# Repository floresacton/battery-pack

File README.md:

# battery-pack
Li-Ion 21700 12S3P Pack

## notes
Battery will have onboard 12V buck regulator for aux power (5A-10A)
This will also have double gated 12V to external aux power

12V -> 5V buck regulator for mini aux power (VCC self power effeciency and for BMS util)

BMS takes in 5V and LDO to 3V3

Main BMS: read all cell voltages, balancing, current measure, and dual gate disconnect, temperature
put one thermistor on the board and some on the cells

On the back of the BMS and maybe the regulator, the thermistor connections to measure cell temps

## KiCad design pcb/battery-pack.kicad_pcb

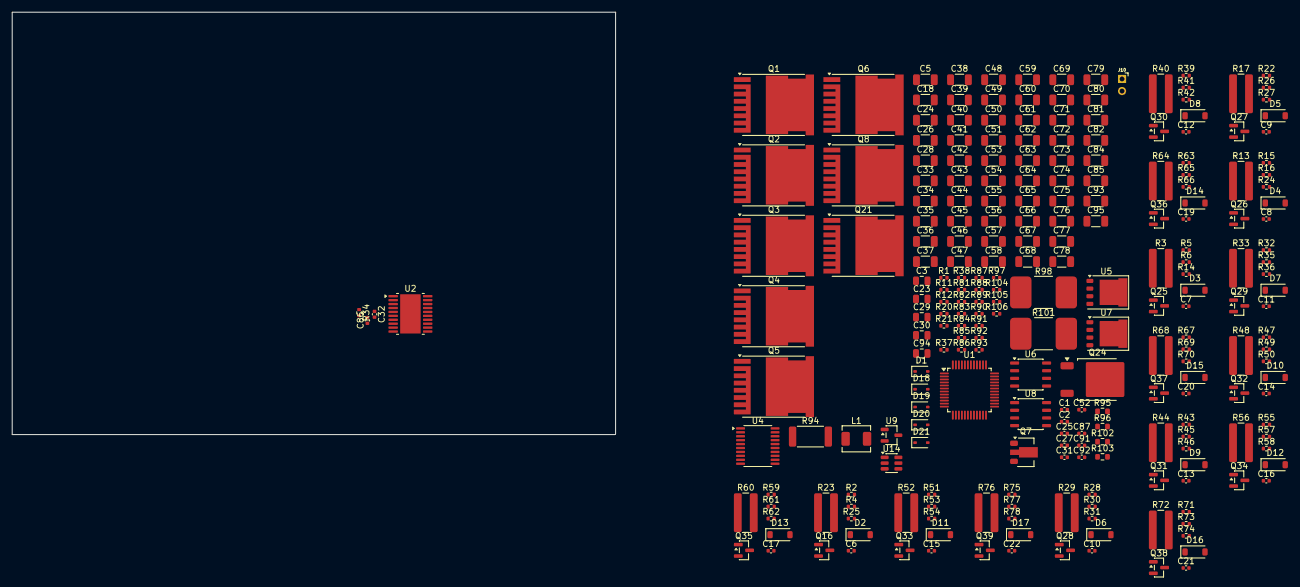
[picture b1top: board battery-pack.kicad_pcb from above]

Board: 4 copper layers, 100.0 x 70.0 mm, 244 parts (0 on the bottom side), 120 nets, no tracks yet.

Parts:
C1, C6, C7, C8, C9, C10, C11, C12, C13, C14, C15, C16, C17, C19, C20, C21, C22, C25, C27, C52, C91, C92: 100n; C_0402_1005Metric
C2, C31: 100p; C_0402_1005Metric
C3, C23, C29, C30, C94: 1u; C_0805_2012Metric
C5, C24, C39, C40, C45, C46, C51, C53, C58, C59, C63, C64, C65, C66, C67, C68, C69, C70, C71, C72, C73, C74, C75, C76, C77, C78, C79, C80, C81, C82, C84, C85: 2u2; C_1206_3216Metric
C18, C26, C28, C33, C34, C35, C36, C37, C38, C41, C42, C43, C44, C47, C48, C49, C50, C54, C55, C56, C57, C60, C61, C62, C93, C95: 10u; C_1206_3216Metric
C32: 1n; C_0402_1005Metric
C86: 10n; C_0402_1005Metric
C87: 2n2; C_0402_1005Metric
D1, D18, D19, D20, D21: 1N4148WS; D_SOD-323
D2, D3, D4, D5, D6, D7, D8, D9, D10, D11, D12, D13, D14, D15, D16, D17: BZT52C5V6; D_SOD-123
J10: Conn_01x02; 1x02_2.00mm_Solder
L1: 4u7; L_TechFuse_SL0420
Q1, Q2, Q3, Q4, Q5, Q6, Q8, Q21: SP010N01BGHTO; Infineon_PG-HSOF-8-1
Q7: CXT5551; SOT-89-3
Q16, Q25, Q26, Q27, Q28, Q29, Q30, Q31, Q32, Q33, Q34, Q35, Q36, Q37, Q38, Q39: HL2300; SOT-23
Q24: AGM150P10D; TO-252-2
R1, R2, R5, R6, R11, R12, R15, R16, R22, R25, R27, R28, R31, R32, R36, R39, R42, R43, R46, R47, R50, R51, R54, R55, R58, R59, R62, R63, R66, R67, R70, R71, R74, R75, R78, R85, R86, R87, R88, R89: 100; R_0402_1005Metric
R3, R13, R17, R23, R29, R33, R40, R44, R48, R52, R56, R60, R64, R68, R72, R76: 8; R_1225_3264Metric
R4, R14, R20, R21, R24, R26, R30, R35, R38, R41, R45, R49, R53, R57, R61, R65, R69, R73, R77, R81, R82, R83, R84, R90, R92: 2k; R_0402_1005Metric
R34, R104: 12k; R_0402_1005Metric
R37: 22k; R_0402_1005Metric
R91, R93, R97, R105: 33k; R_0402_1005Metric
R94: 3m; R_2512_6332Metric
R95, R96, R102, R103: 1; R_0603_1608Metric
R98, R101: 1m; R_Shunt_3921
R106: 2k2; R_0402_1005Metric
U1: BQ7695202; TQFP-48_7x7mm_P0.5mm
U2: LM5116; HTSSOP-20-1EP_4.4x6.5mm_P0.65mm_EP3.4x6.5mm_Mask2.4x3.7mm
U4: STM32C011F6Px; TSSOP-20_4.4x6.5mm_P0.65mm
U5, U7: AGM042N10A; PQFN-8-EP_6x5mm_P1.27mm_Generic
U6: SP485E; JEITA_SOIC-8_3.9x4.9mm_P1.27mm
U8: IRS2181STR; JEITA_SOIC-8_3.9x4.9mm_P1.27mm
U9: XC6206PxxxMR; SOT-23-3
U14: JW5017S; SOT-23-6

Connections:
+3V3: C23.1, D18.1 (K), R20.2, R21.2, U1.35 (REG1), U4.4 (VDD)
+5V: C26.1, C52.2, C92.2, C93.1, C95.1, L1.2, R104.2, U6.8 (VCC), U9.3 (VI)
+15V: C28.1, C34.1, C35.1, C36.1, C37.1, C38.1, C41.1, C42.1, C43.1, C44.1, C47.1, C48.1, C49.1, C50.1, C54.1, C55.1, C56.1, C57.1, C60.1, C61.1, C62.1, D19.2 (A), R37.2, R105.2, U2.10 (VOUT), U2.17 (VCCX), U8.5 (VCC), U14.5 (VIN)
/BREG: Q7.1 (B), U1.37 (BREG)
/BST: C33.1, D19.1 (K), U8.8 (VB)
/BT: C91.1, U14.1 (BST)
/CL1: D3.2 (A), Q25.2 (S), R2.2, R5.2, R23.1
/CL2: D4.2 (A), Q26.2 (S), R3.1, R6.2, R15.2
/CL3: D5.2 (A), Q27.2 (S), R13.1, R16.2, R27.2
/CL4: D6.2 (A), Q28.2 (S), R17.1, R22.2, R31.2
/CL5: D7.2 (A), Q29.2 (S), R28.2, R29.1, R36.2
/CL6: D8.2 (A), Q30.2 (S), R32.2, R33.1, R42.2
/CL7: D9.2 (A), Q31.2 (S), R39.2, R40.1, R46.2
/CL8: D10.2 (A), Q32.2 (S), R43.2, R44.1, R50.2
/CL9: D11.2 (A), Q33.2 (S), R47.2, R48.1, R54.2
/CL10: D12.2 (A), Q34.2 (S), R51.2, R52.1, R58.2
/CL11: D13.2 (A), Q35.2 (S), R55.2, R56.1, R62.2
/CL12: D14.2 (A), Q36.2 (S), R59.2, R60.1, R66.2
/CL13: D15.2 (A), Q37.2 (S), R63.2, R64.1, R70.2
/CL14: D16.2 (A), Q38.2 (S), R67.2, R68.1, R74.2
/CL15: D17.2 (A), Q39.2 (S), R71.2, R72.1, R78.2
/CMP: C31.1, R97.2, U2.9 (COMP)
/CP: C3.1, U1.46 (CP1)
/CS: R94.1, U2.12 (CS), U5.1 (S), U5.2 (S), U5.3 (S)
/DSG: Q1.1 (G), Q8.1 (G), Q21.1 (G), U1.43 (DSG)
/FB: C31.2, C87.1, R37.1, R38.2, R104.1, R106.1, U2.8 (FB), U14.3 (FB)
/GCH: R103.1, U8.7 (HO)
/GCL: R102.1, U8.4 (LO)
/GD: Q3.1 (G), Q4.1 (G)
/GH: Q2.1 (G), Q5.1 (G), R103.2
/HB: C30.1, D20.1 (K), U2.18 (HB)
/HO: R96.1, U2.19 (HO)
/LD: R82.1, U1.41 (LD)
/LO: R95.1, U2.15 (LO)
/PACK: R81.1, U1.42 (PACK)
/PH: C33.2, Q2.2 (S), Q5.2 (S), Q6.3 (D), U8.6 (VS)
/RAMP: C32.1, U2.5 (RAMP)
/REG18: C18.1, U1.24 (REG18)
/REGIN: C25.2, Q7.3 (E), U1.36 (REGIN)
/RSA: J10.2, R88.2, R89.2, U6.6 (A)
/RSB: J10.1, R86.1, R87.1, U6.7 (B)
/RT: R34.1, U2.3 (RT)
/SCL: R20.1, U1.26 (SCL)
/SDA: R21.1, U1.27 (SDA)
/SPL: C27.2, R86.2, R87.2, R88.1, R89.1
/SRN: C1.1, C2.1, R12.1, U1.20 (SRN)
/SRP: C1.2, C2.2, R11.1, U1.18 (SRP)
/SS: C86.1, U2.7 (SS)
/SW: C30.2, C91.2, L1.1, U2.20 (SW), U5.5 (D), U7.1 (S), U7.2 (S), U7.3 (S), U14.6 (SW)
/UVLO: R91.1, R92.2, U2.2 (UVLO)
/VC0: C6.1, R4.1, R25.1, U1.16 (VC0)
/VC1: C6.2, C7.1, R2.1, R5.1, R14.1, U1.15 (VC1)
/VC2: C7.2, C8.1, R6.1, R15.1, R24.1, U1.14 (VC2)
/VC3: C8.2, C9.1, R16.1, R26.1, R27.1, U1.13 (VC3)
/VC4: C9.2, C10.1, R22.1, R30.1, R31.1, U1.12 (VC4)
/VC5: C10.2, C11.1, R28.1, R35.1, R36.1, U1.11 (VC5)
/VC6: C11.2, C12.1, R32.1, R41.1, R42.1, U1.10 (VC6)
/VC7: C12.2, C13.1, R39.1, R45.1, R46.1, U1.9 (VC7)
/VC8: C13.2, C14.1, R43.1, R49.1, R50.1, U1.8 (VC8)
/VC9: C14.2, C15.1, R47.1, R53.1, R54.1, U1.7 (VC9)
/VC10: C15.2, C16.1, R51.1, R57.1, R58.1, U1.6 (VC10)
/VC11: C16.2, C17.1, R55.1, R61.1, R62.1, U1.5 (VC11)
/VC12: C17.2, C19.1, R59.1, R65.1, R66.1, U1.4 (VC12)
/VC13: C19.2, C20.1, R63.1, R69.1, R70.1, U1.3 (VC13)
/VC14: C20.2, C21.1, R67.1, R73.1, R74.1, U1.2 (VC14)
/VC15: C21.2, C22.1, R71.1, R77.1, R78.1, U1.1 (VC15)
/VC16: C22.2, R75.1, U1.48 (VC16)
/VCCR: C29.1, D20.2 (A), U2.16 (VCC)
GBAT: C5.2, C18.2, C23.2, C24.2, C25.1, D2.2 (A), Q16.2 (S), R11.2, R25.2, R90.1, U1.17 (VSS), U1.34 (REG2), U1.38 (FUSE)
GND: C26.2, C27.1, C28.2, C29.2, C32.2, C34.2, C35.2, C36.2, C37.2, C38.2, C39.2, C40.2, C41.2, C42.2, C43.2, C44.2, C45.2, C46.2, C47.2, C48.2, C49.2, C50.2, C51.2, C52.1, C53.2, C54.2, C55.2, C56.2, C57.2, C58.2, C59.2, C60.2, C61.2, C62.2, C63.2, C64.2, C65.2, C66.2, C67.2, C68.2, C69.2, C70.2, C71.2, C72.2, C73.2, C74.2, C75.2, C76.2, C77.2, C78.2, C79.2, C80.2, C81.2, C82.2, C84.2, C85.2, C86.2, C92.1, C93.2, C94.2, C95.2, Q6.2 (S), R12.2, R34.2, R38.1, R92.1, R94.2, R106.2, U2.6 (AGND), U2.11 (DEMB), U2.13 (CSG), U2.14 (PGND), U2.21 (EP), U4.5 (VSS), U6.5 (GND), U8.3 (COM), U9.1 (GND), U14.2 (GND)
unnamed: C87.2, R97.1
unnamed: D1.1 (K), R1.1
unnamed: D2.1 (K), Q16.1 (G), R4.2
unnamed: D3.1 (K), Q25.1 (G), R14.2
unnamed: D4.1 (K), Q26.1 (G), R24.2
unnamed: D5.1 (K), Q27.1 (G), R26.2
unnamed: D6.1 (K), Q28.1 (G), R30.2
unnamed: D7.1 (K), Q29.1 (G), R35.2
unnamed: D8.1 (K), Q30.1 (G), R41.2
unnamed: D9.1 (K), Q31.1 (G), R45.2
unnamed: D10.1 (K), Q32.1 (G), R49.2
unnamed: D11.1 (K), Q33.1 (G), R53.2
unnamed: D12.1 (K), Q34.1 (G), R57.2
unnamed: D13.1 (K), Q35.1 (G), R61.2
unnamed: D14.1 (K), Q36.1 (G), R65.2
unnamed: D15.1 (K), Q37.1 (G), R69.2
unnamed: D16.1 (K), Q38.1 (G), R73.2
unnamed: D17.1 (K), Q39.1 (G), R77.2
unnamed: C94.1, D18.2 (A), U9.2 (VO)
unnamed: D21.1 (K), R85.1
unnamed: R98.1, R101.1
unnamed: Q2.3 (D), Q5.3 (D), R98.2, R101.2
unnamed: Q3.3 (D), Q4.3 (D)
unnamed: Q6.1 (G), R102.2
unnamed: C24.1, Q7.2 (C), R85.2
unnamed: Q16.3 (D), R23.2
unnamed: Q25.3 (D), R3.2
unnamed: Q26.3 (D), R13.2
unnamed: Q27.3 (D), R17.2
unnamed: Q28.3 (D), R29.2
unnamed: Q29.3 (D), R33.2
unnamed: Q30.3 (D), R40.2
unnamed: Q31.3 (D), R44.2
unnamed: Q32.3 (D), R48.2
unnamed: Q33.3 (D), R52.2
unnamed: Q34.3 (D), R56.2
unnamed: Q35.3 (D), R60.2
unnamed: Q36.3 (D), R64.2
unnamed: Q37.3 (D), R68.2
unnamed: Q38.3 (D), R72.2
unnamed: Q39.3 (D), R76.2
unnamed: R81.2, R84.1
unnamed: R82.2, R83.1
unnamed: R91.2, R93.1
unnamed: C3.2, C5.1, R1.2, U1.47 (BAT)
unnamed: R95.2, U5.4 (G)
unnamed: R96.2, U7.4 (G)
unnamed: R105.1, U14.4 (EN)
VBAT: D1.2 (A), D21.2 (A), Q1.3 (D), Q8.3 (D), Q21.3 (D), R75.2, R76.1
VBUS: C39.1, C40.1, C45.1, C46.1, C51.1, C53.1, C58.1, C59.1, C63.1, C64.1, C65.1, C66.1, C67.1, C68.1, C69.1, C70.1, C71.1, C72.1, C73.1, C74.1, C75.1, C76.1, C77.1, C78.1, C79.1, C80.1, C81.1, C82.1, C84.1, C85.1, Q1.2 (S), Q3.2 (S), Q4.2 (S), Q8.2 (S), Q21.2 (S), R83.2, R84.2, R93.2, U2.1 (VIN), U7.5 (D)

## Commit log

2025-08-28 Save bms descrete prototype
2025-08-29 Simulate discharge fets
2025-08-31 Save bms sim
2025-08-31 Save pcb
2025-08-31 Init regulator sim
2025-08-31 Save
